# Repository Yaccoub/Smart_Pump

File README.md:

## Smart Pressure Driven Microfluidic Pump

Precise control of flow rate has always been a critical process for most microfluidic applications and research experiments in various fields such as biochemistry, nanotechnology, and biotechnology. In this project, we conceptualized and developed a smart pressure driven pump capable of transporting microfluids at a stable minimum flow rate as low as 0, 1µl/min while providing a user friendly usage experience. With the achieved high-precision control of the liquid flow and the submillisecond response time, our DIY smart pump largely competes with its industrial alternatives at a fraction of the cost (250€ vs 1850€).

Smart Pump : Controlling flow rate has always been a critical process for most microfluidic applications and research
experiments. In this project, we conceptualized and developed a pressure driven pump to deliver flow and provide
the best control of the fluids at a microfluidic scale.

 * For a full description of the project, please read the project documentation included
 in the repository:

   ```https://github.com/Yaccoub/smart_pump/blob/main/documentation/Smart_Pump_Lab_Work_documentation.pdf```

 * To submit bug reports and feature suggestions, or track changes:

     ```https://github.com/Yaccoub/smart_pump/issues```

# Getting Started

With the achieved high-precision control of the liquid flow and the subseconds response time, our
pump system can largely compete with industrial alternatives at a fraction of the cost. As shown in the
droplet experiments (see documentation), our device system can be a viable alternative to costly industrial pressure driven
pumps for most of the research application

These instructions will guide through the project for development and testing purposes.

Clone this repo to your local machine using:

```
git clone https://github.com/Yaccoub/smart_pump.git
```

* The folder naming in this project follows the pattern:

    ```hardware        --> housing and pcb data```

    ```software        --> simulations, microcontroller and GUI```
    
    ```documentation        --> documentation of the project```
    
 Prerequisites
-------------

This project requires the following modules:

 * Matlab Release 2020a     (https://de.mathworks.com/products/matlab.html)
 * Arduino IDE 1.8.15       (https://www.arduino.cc/en/software)

## Versioning

We use [Git](https://github.com/) for versioning. For the versions available, see the [tags on this repository](https://github.com/Yaccoub/smart_pump).

## Authors

* **Alaeddine Yacoub** - *alaeddine.yacoub@tum.de* -
* **Daniel Kühbacher** - *daniel.kuehbacher@tum.de* -
* **Oumaima Zneidi** - *oumaima.zneidi@tum.de* -

## License

This project is licensed under the TranslaTUM - Central Institute for Translational Cancer Research

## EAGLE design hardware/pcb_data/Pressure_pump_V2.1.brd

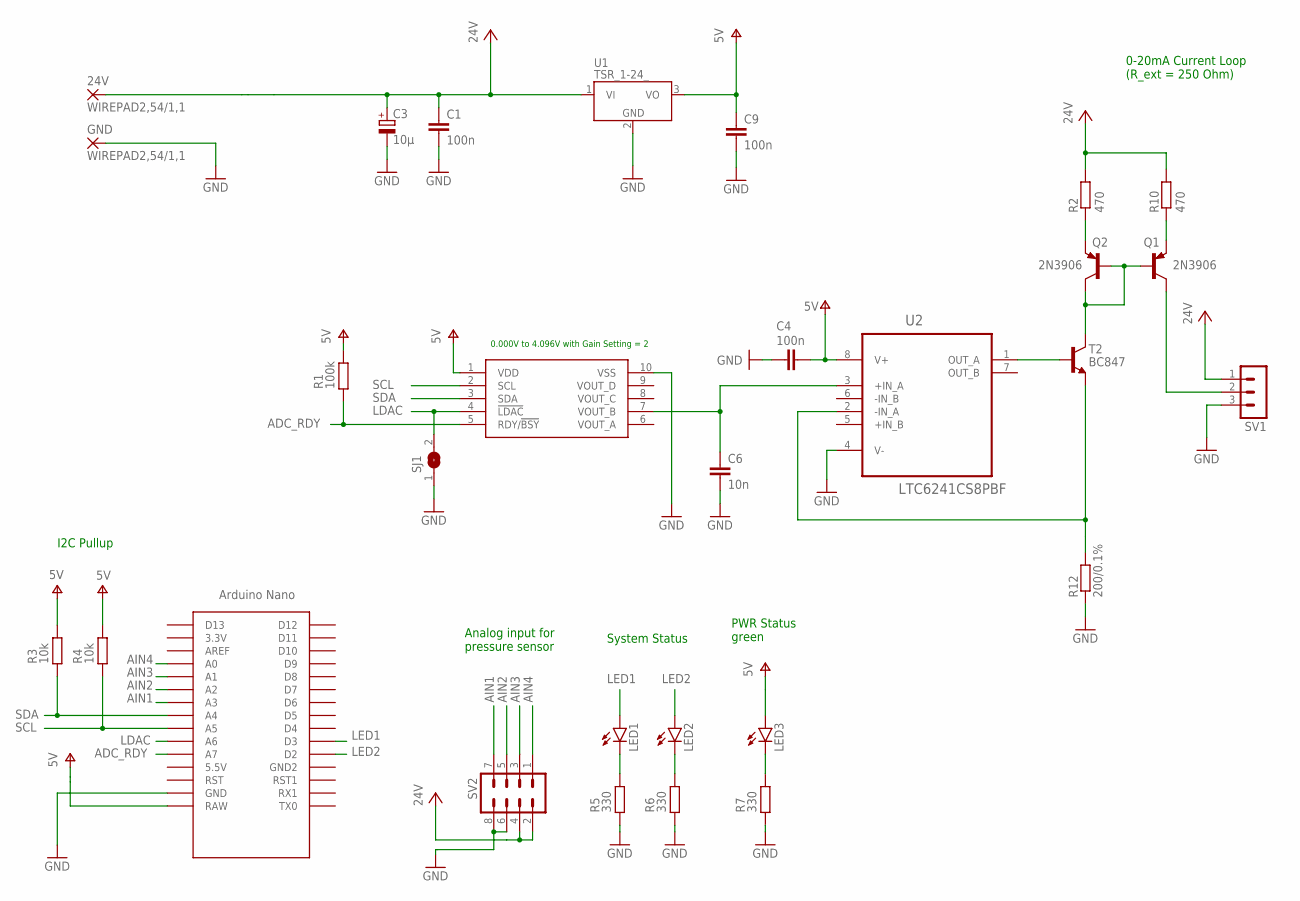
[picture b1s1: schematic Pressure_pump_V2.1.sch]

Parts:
24V: WIREPAD2,54/1,1; 2,54/1,1
C1, C4, C9: 100n; C0603
C3: 10µ; 153CLV-0810
C6: 10n; C0603
GND: WIREPAD2,54/1,1; 2,54/1,1
LED1, LED2, LED3: LED5MM
Q1, Q2: 2N3906; TO92
R1: 100k; R0603
R2, R10: 470; R0603
R3, R4: 10k; R0603
R5, R6, R7: 330; R0603
R12: 200/0.1%; R0805
SJ1: SJ
SV1: MA03-1
SV2: MA04-2
T2: BC847; SOT23
U1: TSR_1-24_; TSR-1
U2: LTC6241CS8PBF; SOIC127P600X175-8N
U$1: NANO
U$2: MCP4728; MSOP10

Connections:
24V: 24V.1, C1.1, C3.+, R2.2, R10.2, SV1.1, SV2.2, SV2.4, U1.1 (VI)
ADC_RDY: R1.1, U$1.A7, U$2.5 (RDY/!BSY)
AIN1: SV2.7, U$1.A3
AIN2: SV2.5, U$1.A2
AIN3: SV2.3, U$1.A1
AIN4: SV2.1, U$1.A0
GND: C1.2, C3.-, C4.1, C6.2, C9.2, GND.1, R5.1, R6.1, R7.1, R12.1, SJ1.1, SV1.3, SV2.6, SV2.8, U1.2 (GND), U2.4 (V-), U$1.GND, U$2.10 (VSS)
LDAC: SJ1.2, U$1.A6, U$2.4 (!LDAC)
LED1: LED1.A, U$1.D3
LED2: LED2.A, U$1.D2
unnamed: Q1.1 (C), SV1.2
unnamed: Q1.3 (E), R10.1
unnamed: Q1.2 (B), Q2.1 (C), Q2.2 (B), T2.3 (C)
unnamed: Q2.3 (E), R2.1
unnamed: T2.1 (B), U2.1 (OUT_A)
unnamed: LED1.K (C), R5.2
unnamed: LED2.K (C), R6.2
unnamed: LED3.K (C), R7.2
unnamed: C6.1, U2.3 (+IN_A), U$2.7 (VOUT_B)
unnamed: R12.2, T2.2 (E), U2.2 (-IN_A)
SCL: R4.1, U$1.A5, U$2.2 (SCL)
SDA: R3.1, U$1.A4, U$2.3 (SDA)
V+: C4.2, C9.1, LED3.A, R1.2, R3.2, R4.2, U1.3 (VO), U2.8 (V+), U$1.RAW, U$2.1 (VDD)

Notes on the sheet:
I2C Pullup
0-20mA Current Loop (R_ext = 250 Ohm)
PWR Status green
System Status
Analog input for pressure sensor
0.000V to 4.096V with Gain Setting = 2

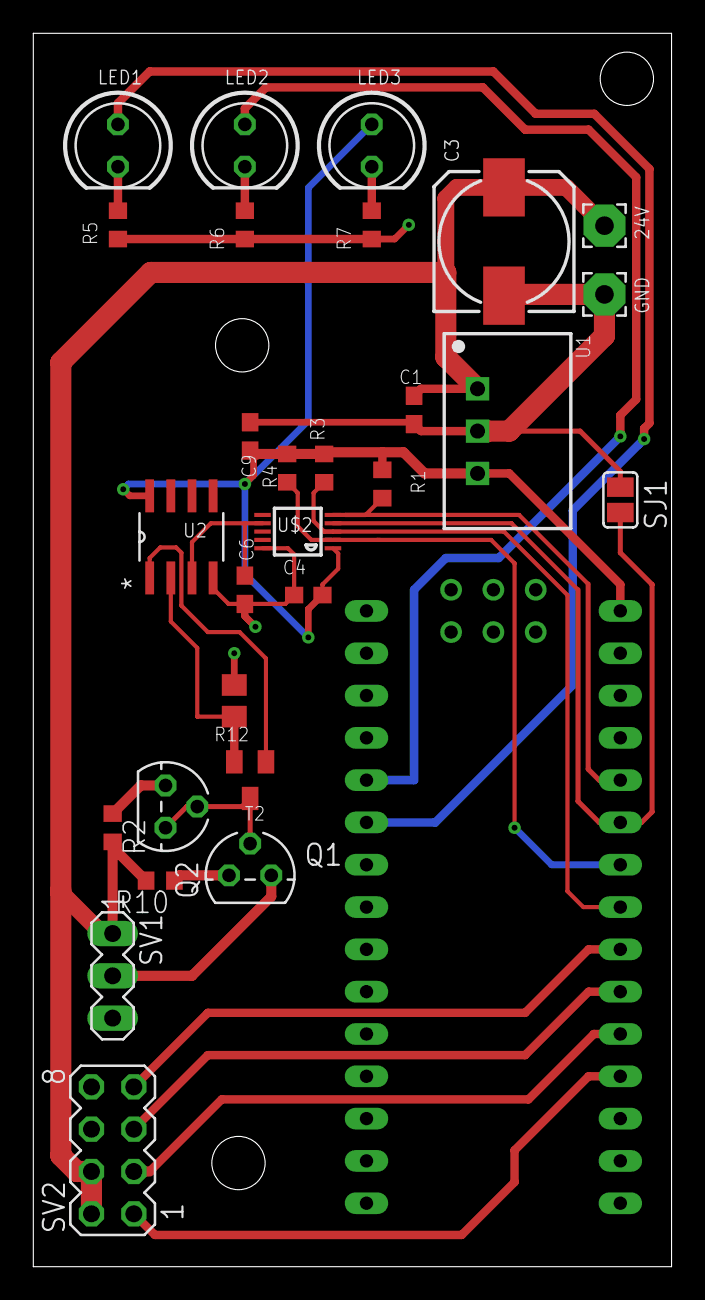
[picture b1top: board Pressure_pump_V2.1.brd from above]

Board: 2 copper layers, 38.3 x 74.0 mm, 29 parts (0 on the bottom side), 23 nets.

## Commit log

2021-09-05 update main_pressure_control
